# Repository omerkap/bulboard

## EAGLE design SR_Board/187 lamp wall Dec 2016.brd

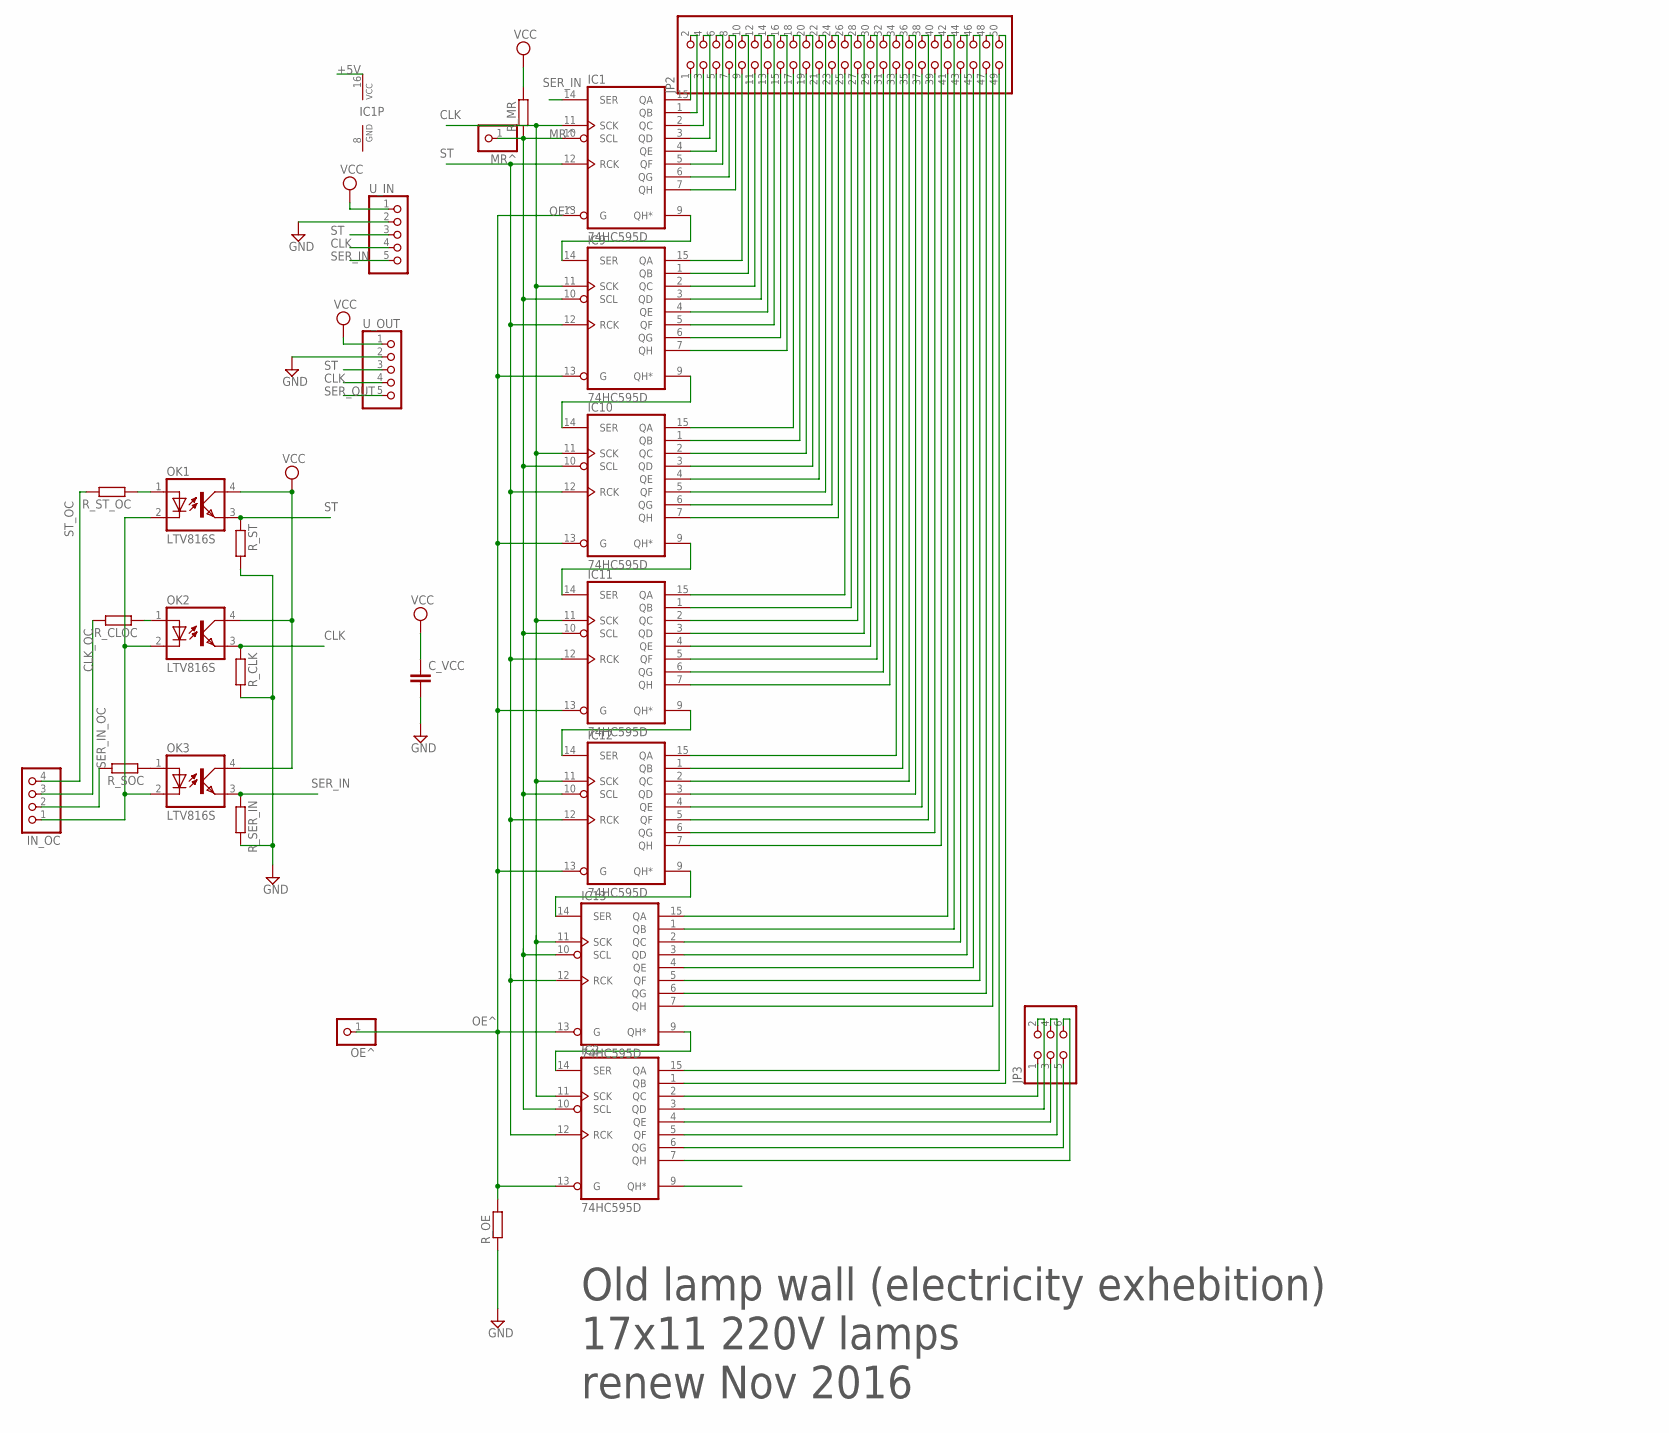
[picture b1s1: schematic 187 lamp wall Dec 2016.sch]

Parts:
C_VCC: C-EUC0603; C0603
IC1, IC2, IC9, IC10, IC11, IC12, IC13: 74HC595D; SO16
IN_OC: PINHD-1X4SMALL_PADS; 1X4MARKED_SMALL
JP2: PINHD-2X25; 2X25
JP3: PINHD-2X3; 2X03
MR^: PINHD-1X1; 1X01
OE^: PINHD-1X1; 1X01
OK1, OK2, OK3: LTV816S; SMD4
R_CLK: R-EU_R0603; R0603
R_CLOC: R-EU_R0603; R0603
R_MR: R-EU_R0603; R0603
R_OE: R-EU_R0603; R0603
R_SER_IN: R-EU_R0603; R0603
R_SOC: R-EU_R0603; R0603
R_ST: R-EU_R0603; R0603
R_ST_OC: R-EU_R0603; R0603
U_IN: PIN_HEAD_1X5_MARKEDSMAOLPAD; 1X5_MARKED_SMALL_PADS
U_OUT: PIN_HEAD_1X5_MARKEDSMAOLPAD; 1X5_MARKED_SMALL_PADS

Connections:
+5V: C_VCC.1, IC1.16 (VCC), IC2.16 (VCC), IC9.16 (VCC), IC10.16 (VCC), IC11.16 (VCC), IC12.16 (VCC), IC13.16 (VCC), OK1.4 (COL), OK2.4 (COL), OK3.4 (COL), R_MR.2, U_IN.1, U_OUT.1
CLK: IC1.11 (SCK), IC2.11 (SCK), IC9.11 (SCK), IC10.11 (SCK), IC11.11 (SCK), IC12.11 (SCK), IC13.11 (SCK), OK2.3 (EMIT), R_CLK.1, U_IN.4, U_OUT.4
CLK_OC: IN_OC.3, R_CLOC.2
GND: C_VCC.2, IC1.8 (GND), IC2.8 (GND), IC9.8 (GND), IC10.8 (GND), IC11.8 (GND), IC12.8 (GND), IC13.8 (GND), R_CLK.2, R_OE.1, R_SER_IN.2, R_ST.2, U_IN.2, U_OUT.2
MR^: IC1.10 (SCL), IC2.10 (SCL), IC9.10 (SCL), IC10.10 (SCL), IC11.10 (SCL), IC12.10 (SCL), IC13.10 (SCL), MR^.1, R_MR.1
unnamed: IC2.15 (QA), JP2.49
unnamed: IC2.1 (QB), JP2.50
unnamed: IC1.15 (QA), JP2.1
unnamed: IC2.2 (QC), JP3.1
unnamed: IC1.1 (QB), JP2.2
unnamed: IC2.3 (QD), JP3.2
unnamed: IC2.4 (QE), JP3.3
unnamed: IC2.5 (QF), JP3.4
unnamed: IC2.6 (QG), JP3.5
unnamed: IC2.7 (QH), JP3.6
unnamed: IC2.14 (SER), IC13.9 (QH*)
unnamed: OK2.1 (A), R_CLOC.1
unnamed: IC1.2 (QC), JP2.3
unnamed: IC1.3 (QD), JP2.4
unnamed: IC1.4 (QE), JP2.5
unnamed: OK1.1 (A), R_ST_OC.1
unnamed: IC1.5 (QF), JP2.6
unnamed: IC1.6 (QG), JP2.7
unnamed: IC1.7 (QH), JP2.8
unnamed: IC1.9 (QH*), IC9.14 (SER)
unnamed: OK3.1 (A), R_SOC.1
unnamed: IC9.15 (QA), JP2.9
unnamed: IC9.1 (QB), JP2.10
unnamed: IC9.2 (QC), JP2.11
unnamed: IC9.3 (QD), JP2.12
unnamed: IC9.4 (QE), JP2.13
unnamed: IN_OC.1, OK1.2 (C), OK2.2 (C), OK3.2 (C)
unnamed: IC9.5 (QF), JP2.14
unnamed: IC9.6 (QG), JP2.15
unnamed: IC9.7 (QH), JP2.16
unnamed: IC9.9 (QH*), IC10.14 (SER)
unnamed: IC10.15 (QA), JP2.17
unnamed: IC10.1 (QB), JP2.18
unnamed: IC10.2 (QC), JP2.19
unnamed: IC10.3 (QD), JP2.20
unnamed: IC10.4 (QE), JP2.21
unnamed: IC10.5 (QF), JP2.22
unnamed: IC10.6 (QG), JP2.23
unnamed: IC10.7 (QH), JP2.24
unnamed: IC11.15 (QA), JP2.25
unnamed: IC11.1 (QB), JP2.26
unnamed: IC11.2 (QC), JP2.27
unnamed: IC11.3 (QD), JP2.28
unnamed: IC11.4 (QE), JP2.29
unnamed: IC11.5 (QF), JP2.30
unnamed: IC11.6 (QG), JP2.31
unnamed: IC11.7 (QH), JP2.32
unnamed: IC12.15 (QA), JP2.33
unnamed: IC12.1 (QB), JP2.34
unnamed: IC12.2 (QC), JP2.35
unnamed: IC12.3 (QD), JP2.36
unnamed: IC12.4 (QE), JP2.37
unnamed: IC12.5 (QF), JP2.38
unnamed: IC12.7 (QH), JP2.40
unnamed: IC13.15 (QA), JP2.41
unnamed: IC13.1 (QB), JP2.42
unnamed: IC13.2 (QC), JP2.43
unnamed: IC13.3 (QD), JP2.44
unnamed: IC13.4 (QE), JP2.45
unnamed: IC13.5 (QF), JP2.46
unnamed: IC13.6 (QG), JP2.47
unnamed: IC13.7 (QH), JP2.48
unnamed: IC10.9 (QH*), IC11.14 (SER)
unnamed: IC11.9 (QH*), IC12.14 (SER)
unnamed: IC12.6 (QG), JP2.39
unnamed: IC12.9 (QH*), IC13.14 (SER)
OE^: IC1.13 (G), IC2.13 (G), IC9.13 (G), IC10.13 (G), IC11.13 (G), IC12.13 (G), IC13.13 (G), OE^.1, R_OE.2
SER_IN: IC1.14 (SER), OK3.3 (EMIT), R_SER_IN.1, U_IN.5
SER_IN_OC: IN_OC.2, R_SOC.2
SER_OUT: IC2.9 (QH*), U_OUT.5
ST: IC1.12 (RCK), IC2.12 (RCK), IC9.12 (RCK), IC10.12 (RCK), IC11.12 (RCK), IC12.12 (RCK), IC13.12 (RCK), OK1.3 (EMIT), R_ST.1, U_IN.3, U_OUT.3
ST_OC: IN_OC.4, R_ST_OC.2

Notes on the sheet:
Old lamp wall (electricity exhebition) 17x11 220V lamps renew Nov 2016

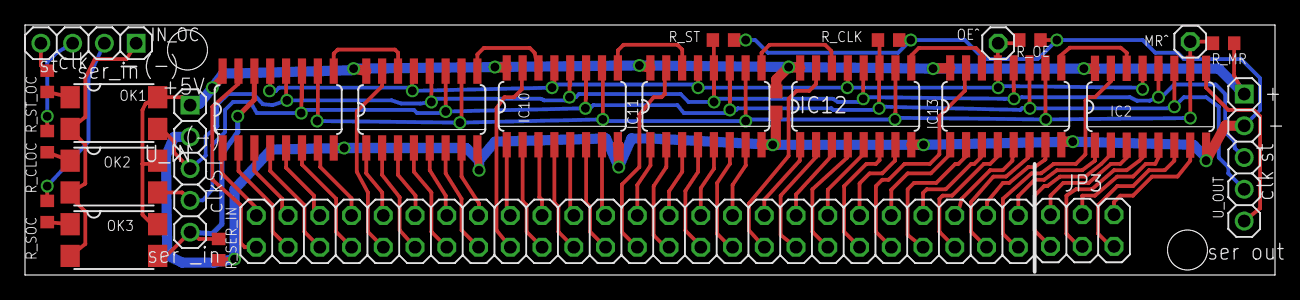
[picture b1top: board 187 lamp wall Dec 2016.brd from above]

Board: 2 copper layers, 100.0 x 20.0 mm, 26 parts (0 on the bottom side), 77 nets.

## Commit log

2017-02-09 [Omer] initial version of sr_driver and Ors camera file
2017-02-16 added eagle files, started to write driver
2017-02-16 added main
2017-02-16 added function to tuggle leds one by one
2017-02-16 moved code to sr_driver.py
2017-02-16 moved code to sr_driver
2017-08-17 initial version of mapped shift register. map is loaded from a csv file
2017-08-17 updated csv
2017-09-07 added demo that runs one led throughout the matrix
2017-09-07 added demo that runs one led throughout the matrix 2
2017-11-08 updates from rpi
2017-11-16 test full registeres
2017-11-16 added game of life test
2017-11-16 some changes to run on pi
2017-11-22 added simulation mode to sr_driver (so we can create an object for testing purpose) started to write messages_writer.py: create text messages for the screen
2017-12-03 add simple gol http server and runner
2017-12-07 added support for rtl strings display
2017-12-07 hanukkah start
2017-12-08 - added an __init__.py file to screen_usages in order to make it a package (and make imports easier) - MessagesWriter now inherits from AbstractScreenUsage - some documentation to MessagesWriter
2017-12-09 [Omer] sovsov initial version
2017-12-09 [Omer] Sovsov is working and emulating with points and scale function
2017-12-09 [Omer] Added line rendering option to sovsov (get_drawable function)
2017-12-11 Static sov with text runner
2017-12-11 for run in hanuka
2018-01-16 created bulboard_server_runner: - run a http server (flask) and update text on bulboard TODO: 1. support hebrew encoding 2. problems with certain characters size (ie. try 'g')
2018-01-23 initial support for bdf fonts (with hebrew)
2018-03-13 some more work on site, created tabs for different usages
2018-04-05 started to work on horizontal message, created layout of button matrix.
2018-04-10 created orchestrator class to change different input methods. now site supports also game of life
2018-04-20 added 'save' button, saves current state and state is loaded in next runs (if pi resets etc.) fixed some utf8 issues - think that now heb/eng text are supported
